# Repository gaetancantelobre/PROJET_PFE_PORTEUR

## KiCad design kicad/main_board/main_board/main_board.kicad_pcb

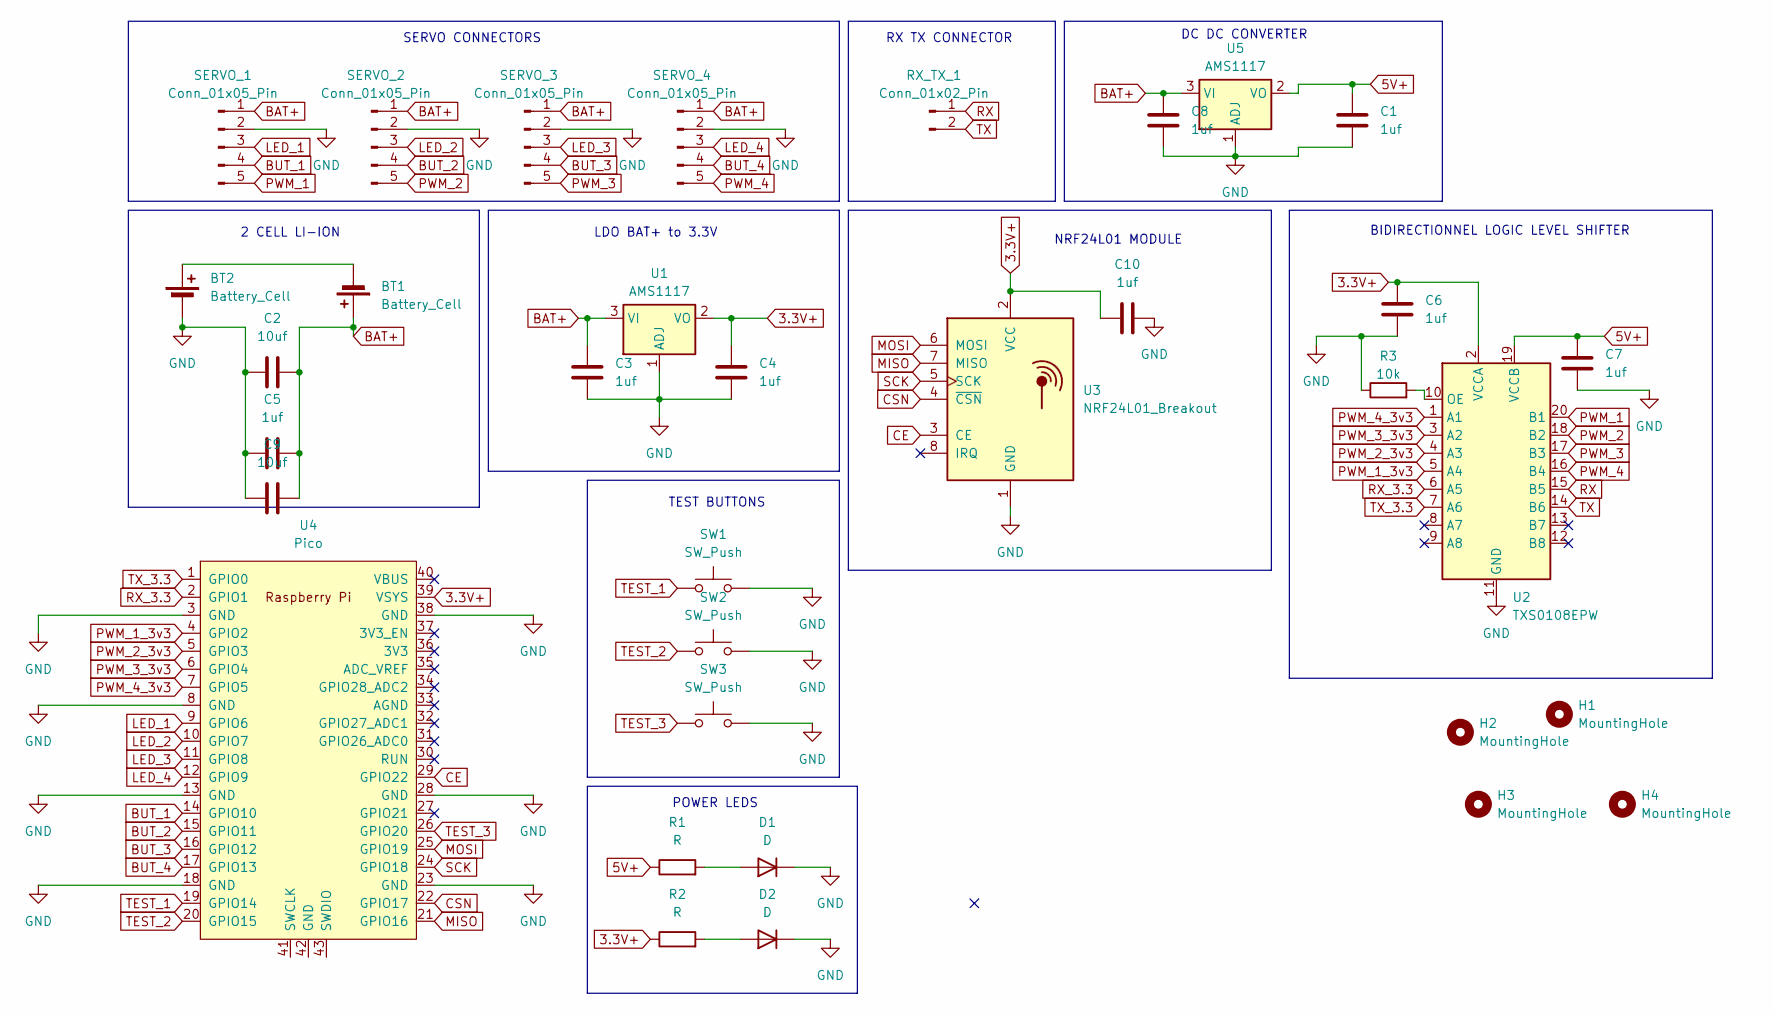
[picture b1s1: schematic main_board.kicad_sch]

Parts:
BT1, BT2: Battery_Cell; BatteryHolder_Keystone_1042_1x18650
C1, C3, C4, C5, C6, C7, C8, C10: 1uf; C_0805_2012Metric
C2, C9: 10uf; CP_Elec_6.3x5.4
D1, D2: D; D_1206_3216Metric
H1, H2, H3, H4: MountingHole; MountingHole_3mm
R1, R2: R; R_1206_3216Metric
R3: 10k; R_1206_3216Metric
RX_TX_1: Conn_01x02_Pin; TerminalBlock_TE_282834-2_1x02_P2.54mm_Horizontal
SERVO_1, SERVO_2, SERVO_3, SERVO_4: Conn_01x05_Pin; TerminalBlock_TE_282834-5_1x05_P2.54mm_Horizontal
SW1, SW2, SW3: SW_Push; SW_PUSH_6mm
U1, U5: AMS1117; SOT-223-3_TabPin2
U2: TXS0108EPW; TSSOP-20_4.4x6.5mm_P0.65mm
U3: NRF24L01_Breakout; nRF24L01_Breakout
U4: Pico; RPi_Pico_SMD_TH

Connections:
3.3V+: C4.1, C6.1, C10.2, R2.1, U1.2 (VO), U2.2 (VCCA), U3.2 (VCC), U4.39 (VSYS)
5V+: C1.1, C7.1, R1.1, U2.19 (VCCB), U5.2 (VO)
BAT+: BT1.1 (+), C2.1, C3.1, C5.1, C8.1, C9.1, SERVO_1.1, SERVO_2.1, SERVO_3.1, SERVO_4.1, U1.3 (VI), U5.3 (VI)
BUT_1: SERVO_1.4, U4.14 (GPIO10)
BUT_2: SERVO_2.4, U4.15 (GPIO11)
BUT_3: SERVO_3.4, U4.16 (GPIO12)
BUT_4: SERVO_4.4, U4.17 (GPIO13)
CE: U3.3 (CE), U4.29 (GPIO22)
CSN: U3.4 (~CSN), U4.22 (GPIO17)
GND: BT2.2 (-), C1.2, C2.2, C3.2, C4.2, C5.2, C6.2, C7.2, C8.2, C9.2, C10.1, D1.1 (K), D2.1 (K), R3.1, SERVO_1.2, SERVO_2.2, SERVO_3.2, SERVO_4.2, SW1.2, SW2.2, SW3.2, U1.1 (ADJ), U2.11 (GND), U3.1 (GND), U4.3 (GND), U4.8 (GND), U4.13 (GND), U4.18 (GND), U4.23 (GND), U4.28 (GND), U4.38 (GND), U5.1 (ADJ)
LED_1: SERVO_1.3, U4.9 (GPIO6)
LED_2: SERVO_2.3, U4.10 (GPIO7)
LED_3: SERVO_3.3, U4.11 (GPIO8)
LED_4: SERVO_4.3, U4.12 (GPIO9)
MISO: U3.7 (MISO), U4.21 (GPIO16)
MOSI: U3.6 (MOSI), U4.25 (GPIO19)
unnamed: BT1.2 (-), BT2.1 (+)
unnamed: D1.2 (A), R1.2
unnamed: D2.2 (A), R2.2
unnamed: R3.2, U2.10 (OE)
PWM_1: SERVO_1.5, U2.20 (B1)
PWM_1_3v3: U2.5 (A4), U4.4 (GPIO2)
PWM_2: SERVO_2.5, U2.18 (B2)
PWM_2_3v3: U2.4 (A3), U4.5 (GPIO3)
PWM_3: SERVO_3.5, U2.17 (B3)
PWM_3_3v3: U2.3 (A2), U4.6 (GPIO4)
PWM_4: SERVO_4.5, U2.16 (B4)
PWM_4_3v3: U2.1 (A1), U4.7 (GPIO5)
RX: RX_TX_1.1, U2.15 (B5)
RX_3.3: U2.6 (A5), U4.2 (GPIO1)
SCK: U3.5 (SCK), U4.24 (GPIO18)
TEST_1: SW1.1, U4.19 (GPIO14)
TEST_2: SW2.1, U4.20 (GPIO15)
TEST_3: SW3.1, U4.26 (GPIO20)
TX: RX_TX_1.2, U2.14 (B6)
TX_3.3: U2.7 (A6), U4.1 (GPIO0)

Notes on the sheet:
LDO BAT+ to 3.3V
SERVO CONNECTORS
RX TX CONNECTOR
NRF24L01 MODULE
TEST BUTTONS
BIDIRECTIONNEL LOGIC LEVEL SHIFTER
POWER LEDS
2 CELL LI-ION
DC DC CONVERTER

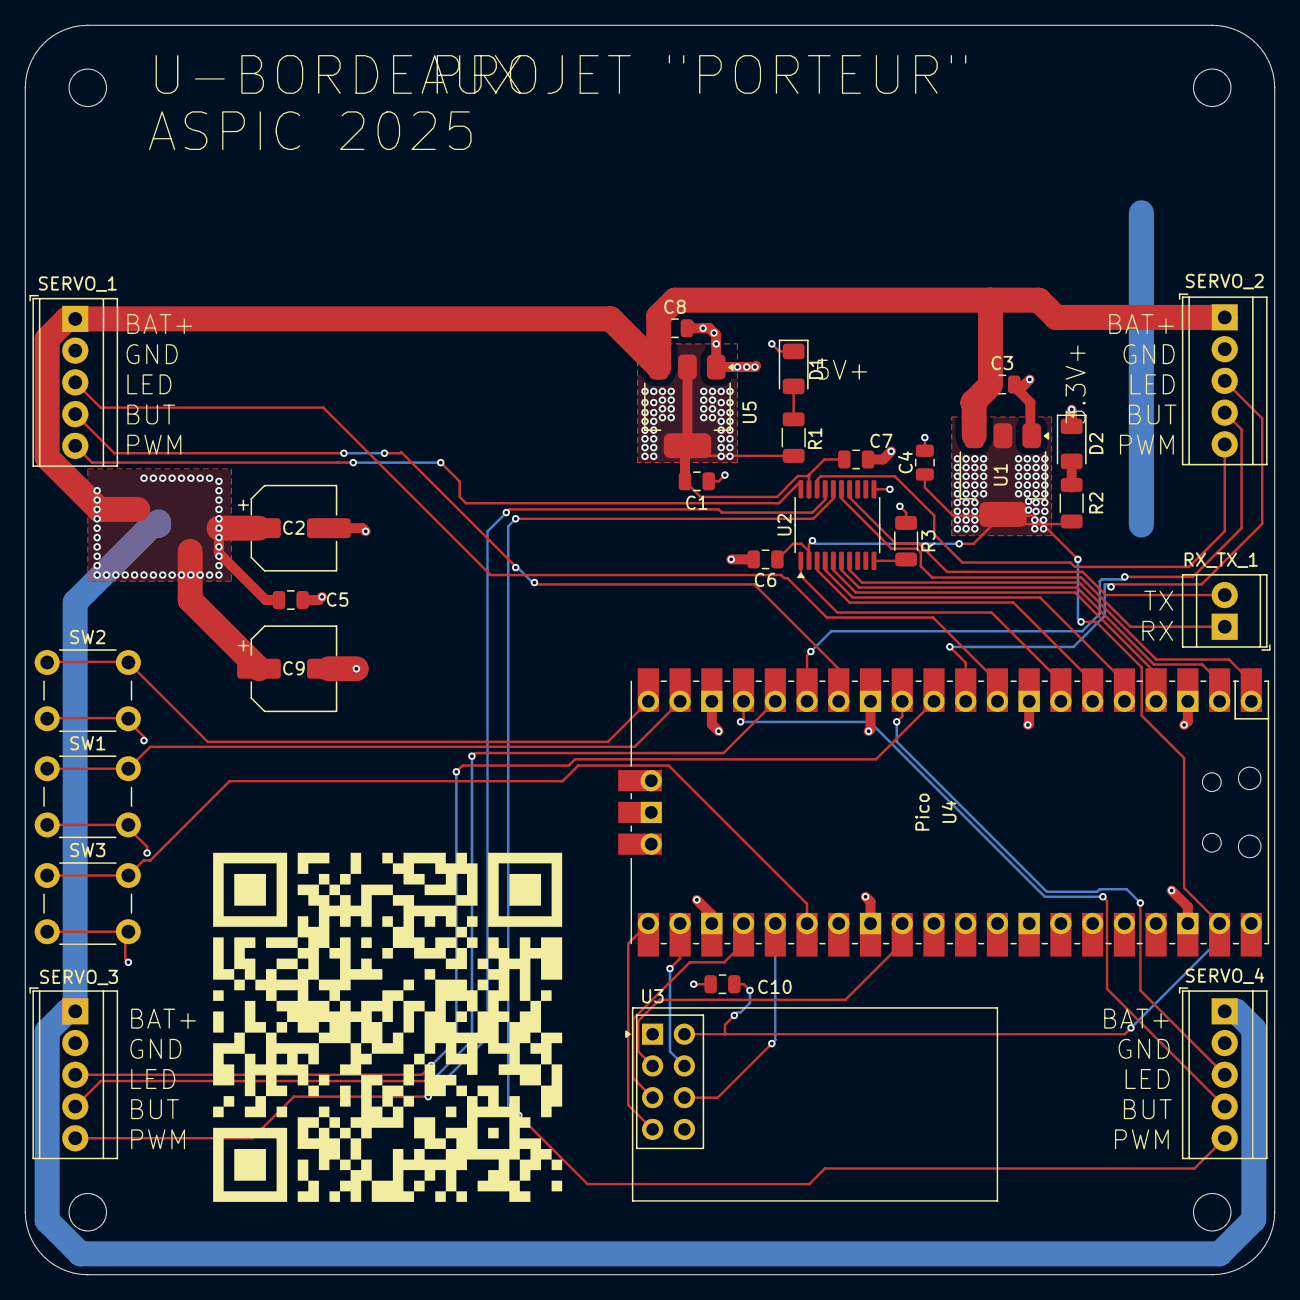
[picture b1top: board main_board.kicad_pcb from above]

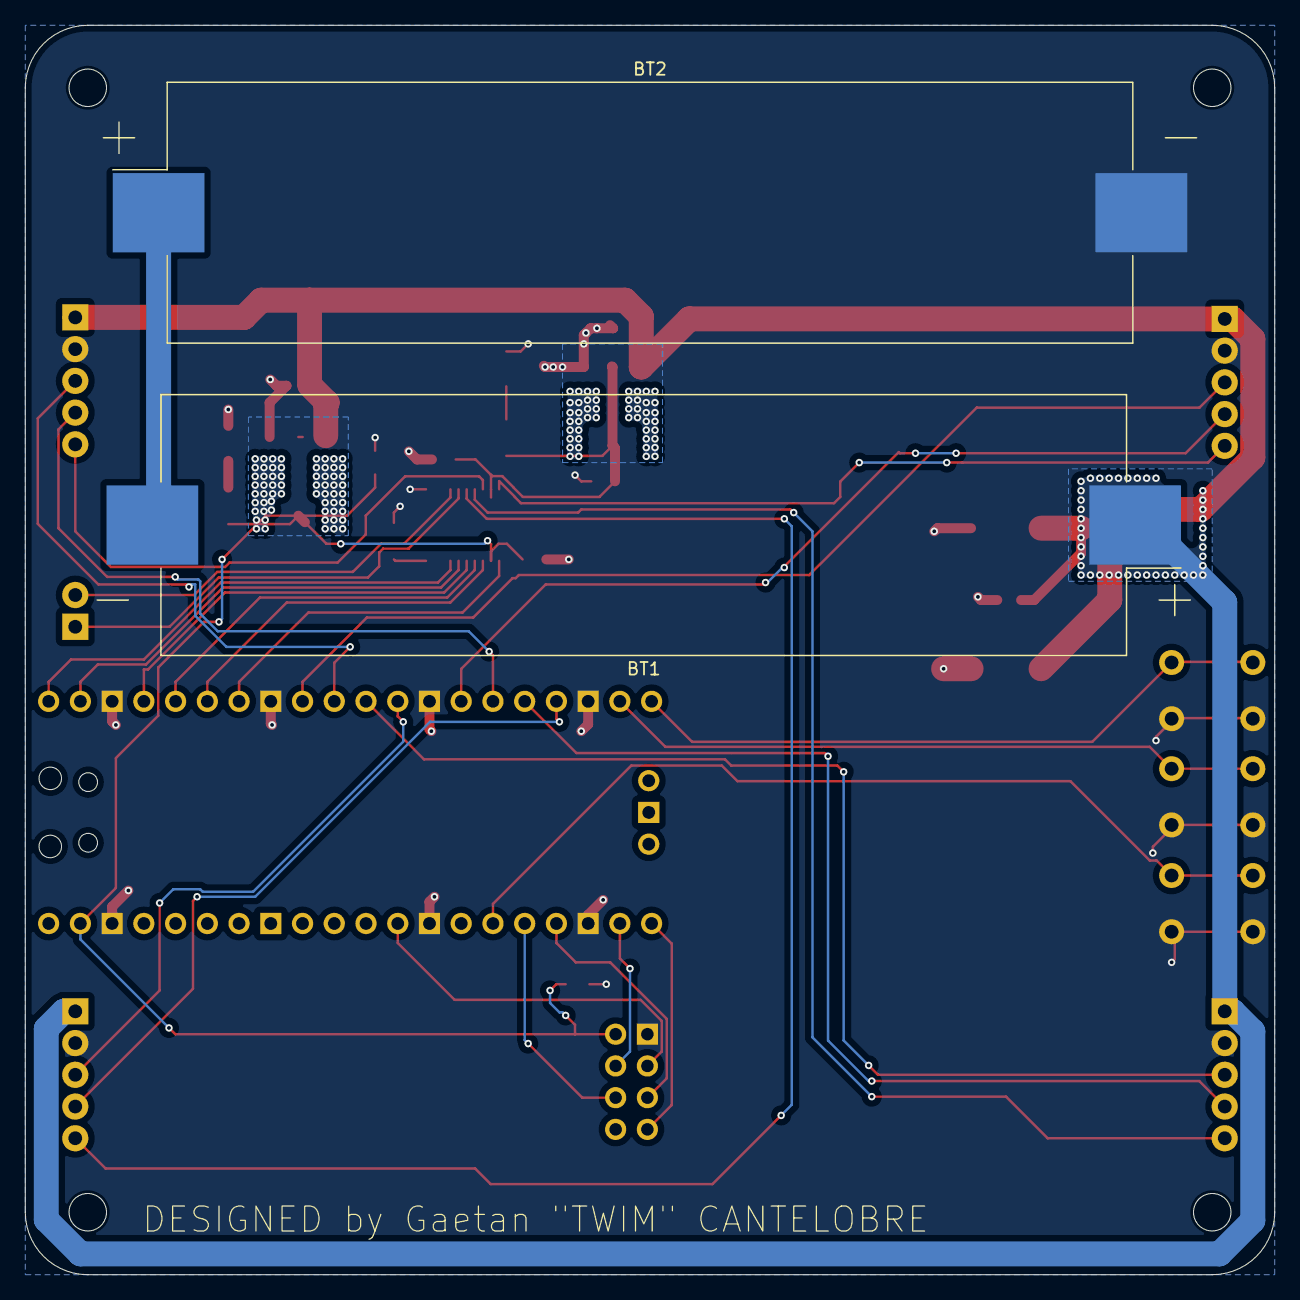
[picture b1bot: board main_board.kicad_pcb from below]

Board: 2 copper layers, 100.0 x 100.0 mm, 34 parts (2 on the bottom side), 36 nets.

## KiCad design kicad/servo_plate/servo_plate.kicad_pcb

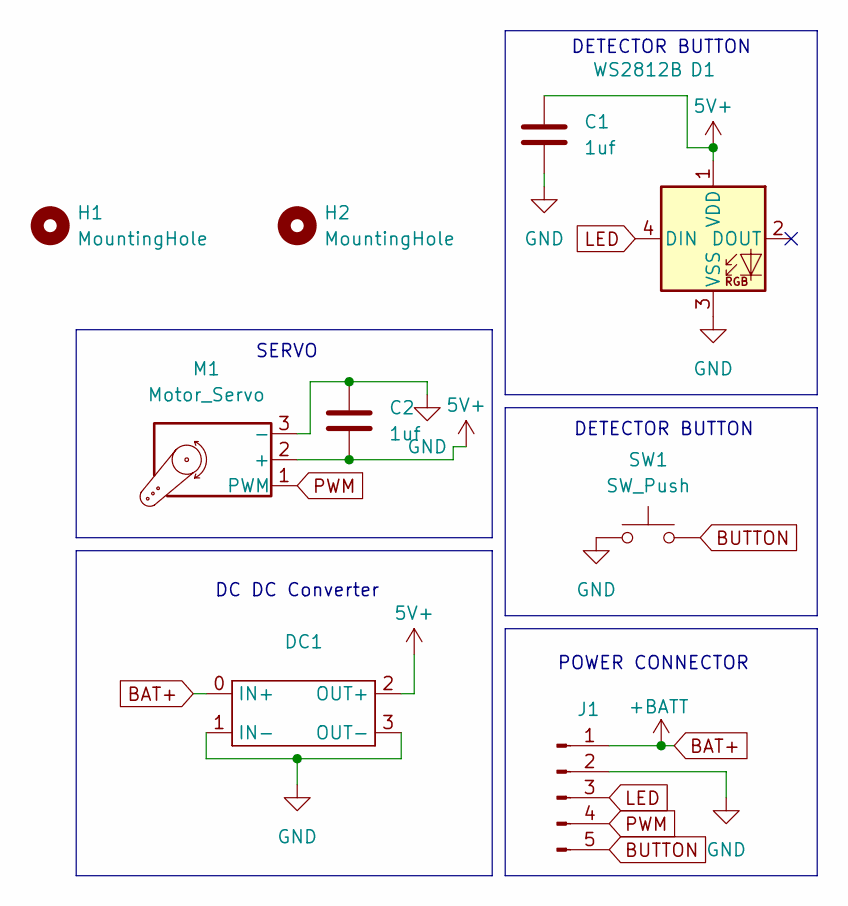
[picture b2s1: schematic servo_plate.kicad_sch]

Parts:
C1, C2: 1uf; C_0805_2012Metric
D1: WS2812B; LED_WS2812B_PLCC4_5.0x5.0mm_P3.2mm
DC1: LM2596_DC_DC_MODULE
H1, H2: MountingHole; MountingHole_3.2mm_M3
J1: Conn_01x05_Pin; TerminalBlock_TE_282834-5_1x05_P2.54mm_Horizontal
M1: Motor_Servo; PinHeader_1x03_P2.54mm_Vertical
SW1: SW_Push; PinHeader_1x02_P2.54mm_Vertical

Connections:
5V+: C1.1, C2.2, D1.1 (VDD), DC1.2 (OUT+), M1.2 (+)
BAT+: DC1.0 (IN+), J1.1
BUTTON: J1.5, SW1.2
GND: C1.2, C2.1, D1.3 (VSS), DC1.1 (IN-), DC1.3 (OUT-), J1.2, M1.3 (-), SW1.1
LED: D1.4 (DIN), J1.3
PWM: J1.4, M1.1 (PWM)

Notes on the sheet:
DETECTOR BUTTON
SERVO
DC DC Converter
POWER CONNECTOR

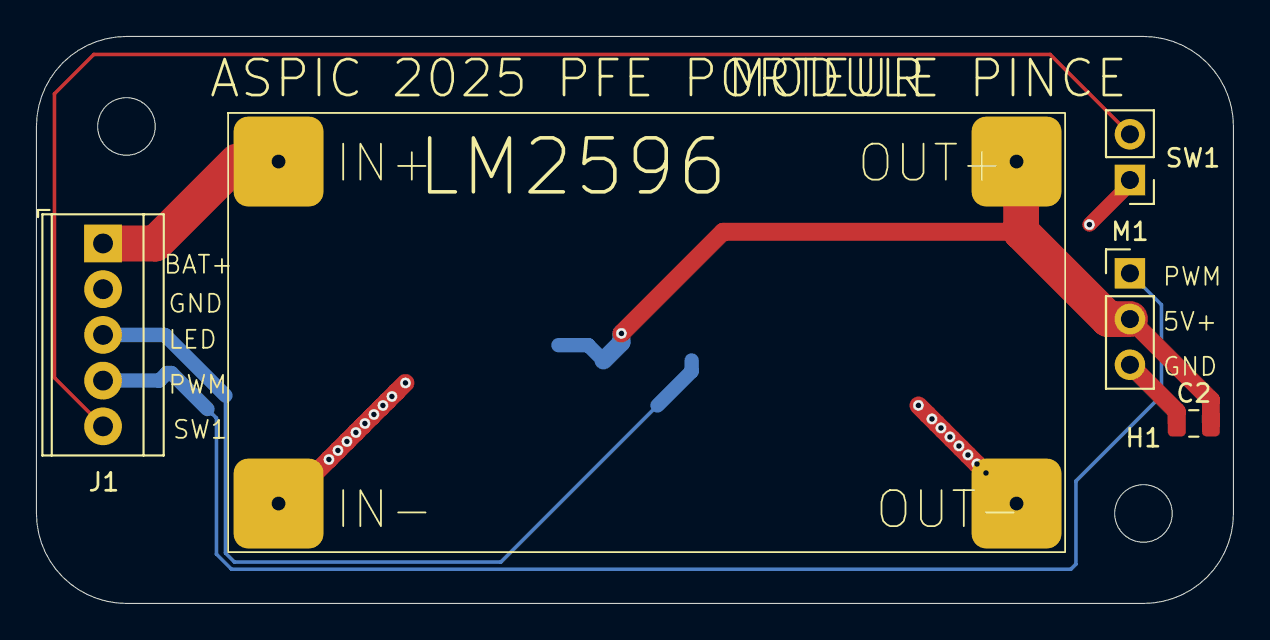
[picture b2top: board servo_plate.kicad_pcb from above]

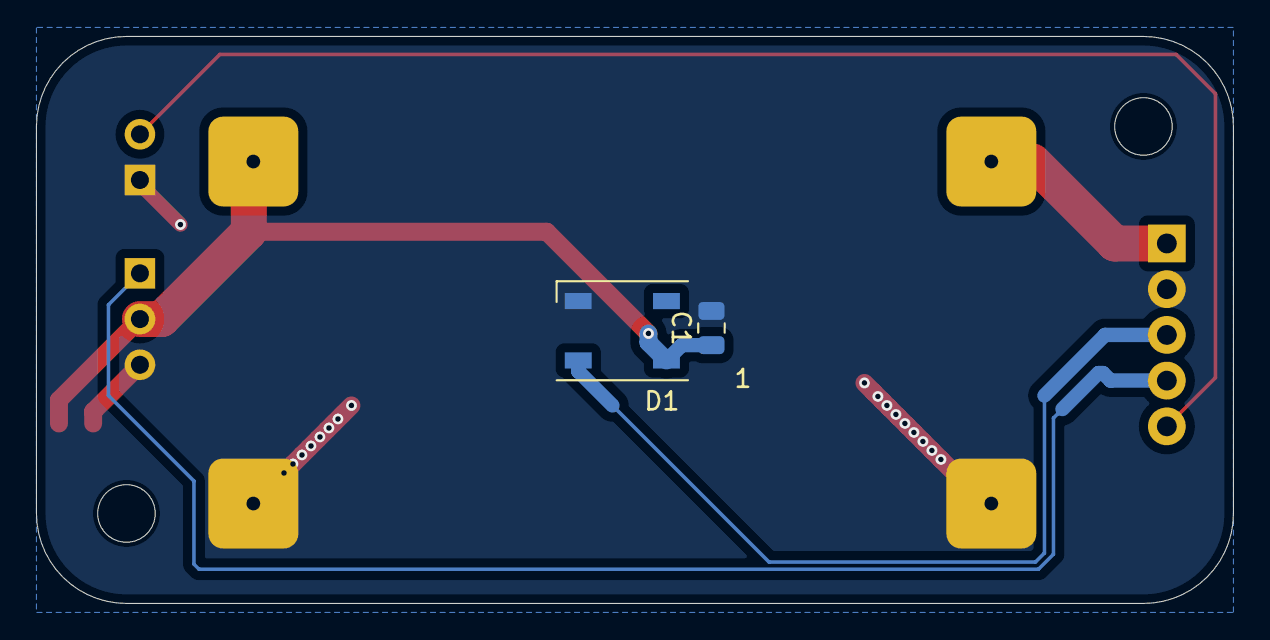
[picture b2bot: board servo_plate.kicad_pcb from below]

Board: 2 copper layers, 66.5 x 31.5 mm, 9 parts (2 on the bottom side), 6 nets.

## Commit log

2025-02-02 [add] : added a pcb
    added the pcb prototype for individual grabber
2025-02-09 added test code for nrf comms
2025-02-10 GANTT file 10/02/2025
    A first version of our GANTT planning
2025-02-13 added gerbers
2025-02-13 added schmetaic for main board
2025-02-14 [feat]final versions of boards + gerbers
2025-02-16 Adding Dockerfile
    First version of the Dockerfile, TODO complete the rest
2025-02-18 Added website for reports
    First bare version for the website where reports, screens, links etc... will be added
2025-02-18 add ptotcode
2025-02-18 Updated version of the website ( CSS and structure done )
    A more advanced version of the website is done, with most of the work unitl week 2 added, only missing its report.
2025-02-18 Updated website for the 3rd week
    Final update for the 3rd week of work, TODO add a section for screenshots, videos etc...
2025-02-18 [feat] add initial project structure and configuration files
2025-02-23 [feat] added serial test python script
    add a test script for serial with the zero W
2025-02-23 [feat] added a BOM file
2025-02-25 Added a non verified V1 plan for the report
    A first version of the report plan, not checked by the teachers yet
2025-02-25 Added V1 final report and timeline
    Added a timeline for the different versions of the final report, along with the first unverified version on it
2025-02-25 [feat] added classes for nacelle control and individual grabber modules
2025-02-25 Added a first version for the tello controller
    first version of the controller
2025-02-25 Functionnal version of the Tello controller
    Adapted version for the Tello Edu controller, made with a command to takeoff and land a few seconds after
2025-02-25 Fix controller
    Removed useless line
2025-02-25 [feat] added test files for pi zero
2025-02-25 [fix] added encoding
2025-02-27 [feat] added most of the functions for the serial communication
2025-02-27 Week 3 update
    Update the website page for the 3rd week report and gantt files
2025-02-28 WIP Demonstration script
    Work in progress for a demonstration script using the throw take off approach
2025-02-28 [feat] added wifi control to drone
2025-03-02 update serial testing code
2025-03-02 testing
2025-03-02 change baudrate
2025-03-02 fix bug
2025-03-02 added arduino code
2025-03-03 [fix] update .gitignore to include additional files and directories; modify gradle.properties to add API key
2025-03-03 [refactor] remove unused buttons and methods; add OnScreenJoystick interface and layout for joystick controls
2025-03-06 added servo angles testing
2025-03-06 added lauche test
2025-03-06 value update
2025-03-06 added loading phase
2025-03-06 added go forward
2025-03-10 added more security to avoid breaking things
2025-03-10 [test] added new loading mechanism
2025-03-10 [fix] fixes some quick bugs
2025-03-10 [fix] added final launch step
2025-03-10 [fix] fixe incorrect servo init
2025-03-10 [feat] added verification before launch
2025-03-10 [feat] added reset button
2025-03-10 [feat] added takeoff for real
2025-03-10 adjusted timings
2025-03-10 Commit for the 4th week report
2025-03-10 [cleaning] cleaned repo
2025-03-11 Added a demonstration video
    Changed the display in order to later add some intresting images about the project, and added a demonstration video to the page
2025-03-12 [feat] added some prints
2025-03-16 added some tweaks
2025-03-16 [refactor] cleaned the branch
2025-03-16 [edit] testing flipping
2025-03-16 [feat] added flipping at the end of the demo for more flare
2025-03-20 [refactor] cleaned repo
2025-03-20 [feat] added json config files
2025-03-21 [refactor] cleaned demo_firmware
2025-03-21 [feat] added better classes to main firmware
2025-03-21 Added the matrice demo
    Commit for the matrice300 flying demon with the flying basket on it
2025-03-26 added stuff before my pc exposed again
2025-03-27 added some majors changes to code
2025-03-27 [fix] fix baudrate value
2025-03-27 [fix] fix incorrect unit usage
2025-03-27 [feat] added hello world and printing recieved messages
2025-03-27 [feat] added esaier debugging
2025-03-27 [feat] added hello world to nacelle to check connection
2025-03-27 [faet] added looping commands
2025-03-27 [fix] bad token
2025-03-27 [fix] bad if cond
2025-03-27 [bug] issue with loading seqeunce crashing
2025-03-27 [bug] still working
2025-03-27 [bug] changed f string
2025-03-27 [feat] added demo mode for the dmeo
2025-03-28 changed settings
2025-04-03 Updated the report chronology
